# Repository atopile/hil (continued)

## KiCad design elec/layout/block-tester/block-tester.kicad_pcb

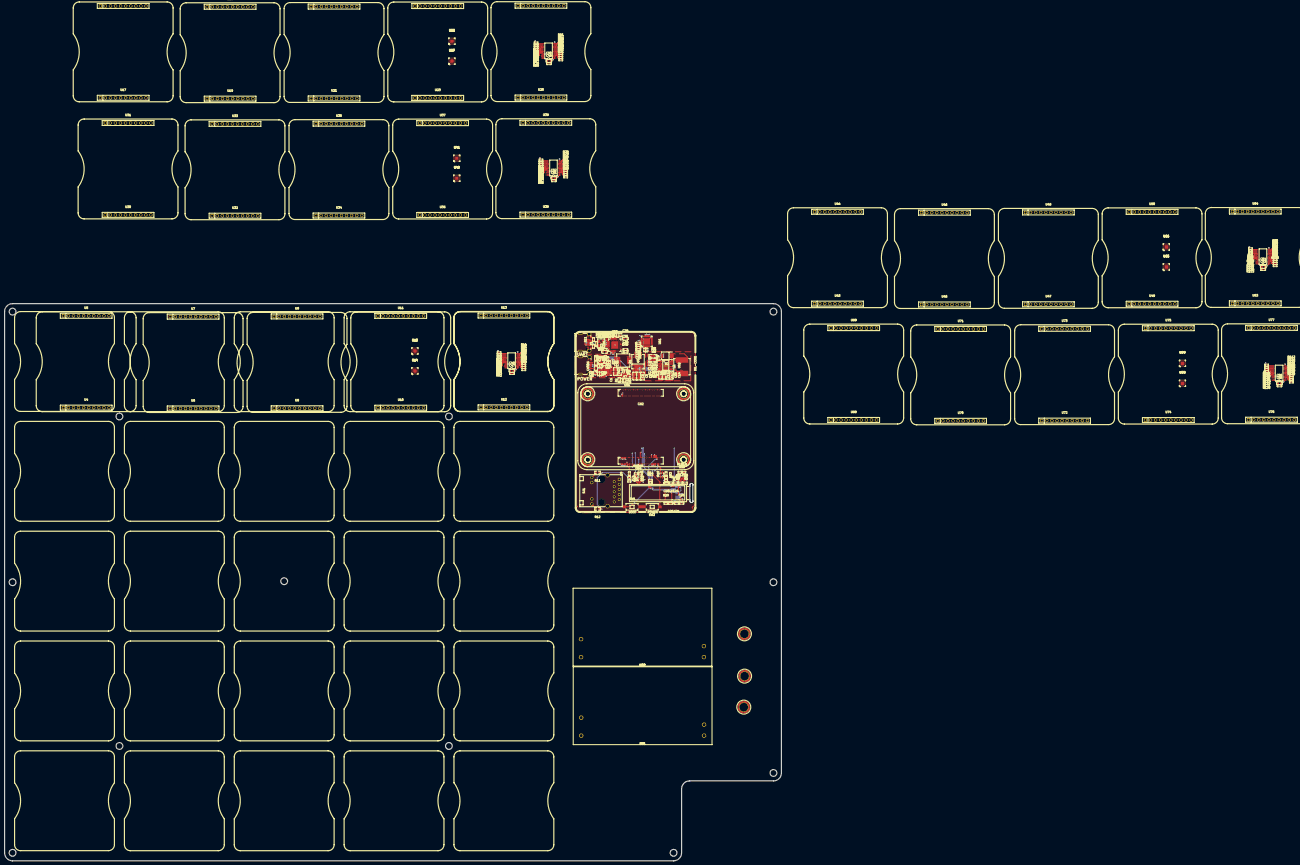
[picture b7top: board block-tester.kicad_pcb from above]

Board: 2 copper layers, 389.0 x 279.0 mm, 279 parts (0 on the bottom side), 306 nets.

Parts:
C1: 6.8nF ±10% 50V X7R; C0402-b3ef17
C2, C3, C4, C5, C6: 10µF ±10% 25V X5R; C0805-3b2e55
C7, C25, C42: 4.7µF ±20% 10V X5R; C0402-b3ef17
C8: 100nF ±10% 50V X7R; C0402-b3ef17
C9: 4.7nF ±5% 50V C0G; C0402-b3ef17
C10: 8.2pF ±5% 50V C0G; C0402-b3ef17
C11, C12, C13: 10µF ±10% 50V X5R; C0805-3b2e55
C14, C15, C16, C17: 22µF ±20% 25V X5R; C0805-3b2e55
C18, C19, C20, C21, C22, C23, C40, C44, C45: 1µF ±10% 25V X5R; C0402-b3ef17
C24, C26, C27, C28, C31, C32, C33, C34, C35, C36, C39, C41, C46, C47, C49, C51, C53, C55: 100nF ±10% 16V X7R; C0402-b3ef17
C29, C30: 10µF ±10% 10V X5R; C0603-bd72f6
C37, C38: 20pF ±5% 50V C0G; C0402-b3ef17
C43: 4.7µF ±10% 35V X5R; C0603-bd72f6
C48, C50, C52, C54, C56: 2.2µF ±10% 16V X5R; C0603-bd72f6
CN1, CN2: CONN-SMD_DF40C-100DS-0.4V-51-ceffa9
D1: SMC_L7.1-W6.2-LS8.1-RD-d9649d
D2: SMB_L4.6-W3.6-LS5.3-RD-330cb3
D3: LED0603-RD-YELLOW-5af84a
D4: LED0603-RD-c81ffb
D5: SOT-323-3_L2.1-W1.3-P1.32-LS2.1-BR-ee9edb
D6, D7: DFN1610-2_L1.6-W1.0-P1.05-RD-57a24e
L1: IND-SMD_L7.1-W6.6-48b69f
L2: IND-SMD_L8.0-W8.0_SWPA8040S-2a70f8
OLED1: OLED-SMD_N087-2832TSWYG02-H14_1-7d3a70
Q1: PDFN3333-8_L3.1-W3.2-P0.65-LS3.4-BL-33e04e
R1, R6, R13, R14, R18, R20, R26, R29, R38, R39, R40, R41, R42, R43, R44, R45, R46, R47, R48, R49, R50, R51, R52, R53, R54, R55, R56, R57, R58, R59, R60, R61, R62, R63, R64, R65, R66, R67, R68, R69, R70, R71, R72, R73, R74, R75, R76, R77, R78, R79, R80, R81, R82, R83, R84, R85, R86, R87, R88, R89, R90, R91, R92, R93, R94, R95, R96, R97, R98, R99, R100, R101, R102, R103, R104, R105, R106, R107, R108, R109, R110, R111, R112, R113, R114, R115, R116, R117, R118, R119, R120, R121, R122: 10kΩ ±1% 62.5mW; R0402-56259e
R2: 180kΩ ±1% 62.5mW; R0402-56259e
R3: 2.49kΩ ±1% 62.5mW; R0402-56259e
R4: 75kΩ ±1% 62.5mW; R0402-56259e
R5: 23.7kΩ ±1% 62.5mW; R0402-56259e
R7: 51kΩ ±1% 62.5mW; R0402-56259e
R8: 162kΩ ±1% 62.5mW; R0402-56259e
R9, R10: 2kΩ ±1% 62.5mW; R0402-56259e
R11, R12: 470Ω ±1% 100mW; R0603-ebcab9
R15: 560Ω ±1% 62.5mW; R0402-56259e
R16, R31, R34: 1kΩ ±1% 62.5mW; R0402-56259e
R17: 510kΩ ±1% 62.5mW; R0402-56259e
R19: 25.5kΩ ±1% 62.5mW; R0402-56259e
R21, R22: 5.1kΩ ±1% 62.5mW; R0402-56259e
R23, R24, R27, R28: 33kΩ ±1% 62.5mW; R0402-56259e
R25: 12kΩ ±1% 62.5mW; R0402-56259e
R30, R32, R33: 4.7kΩ ±1% 62.5mW; R0402-56259e
R35: 100kΩ ±1% 62.5mW; R0402-56259e
R36: 22kΩ ±1% 62.5mW; R0402-56259e
R37: 100Ω ±1% 62.5mW; R0402-56259e
RJ1: RJ45-TH_HR911130A-5845d4
SW1, SW2: SW-SMD_L6.0-W3.3-LS8.0-cfbaed
U1, U2, U3, U54, U55, U56, U57: SMD_BD5.6-D4.1-12eb58
U4, U5, U6, U7, U8, U9, U10, U11, U12, U13, U17, U18, U19, U20, U21, U22, U23, U24, U25, U26, U30, U31, U32, U33, U34, U35, U36, U37, U38, U39, U43, U44, U45, U46, U47, U48, U49, U50, U63, U64, U68, U69, U70, U71, U72, U73, U74, U75, U76, U77: HDR-TH_10P-P2.54-V-F-f96416
U14, U15, U27, U28, U40, U41, U65, U66, U78, U79: QFN-16_L3.0-W3.0-P0.50-BL-EP1.7-3a4c56
U16, U29, U42, U67, U80: TSSOP-24_L7.8-W4.4-P0.65-LS6.4-BL
U51: VQFN-16_L3.0-W3.0-P0.50-BL-EP1.7-62c35a
U52: SOIC-8_L5.0-W4.0-P1.27-LS6.0-BL-EP2.0-748c0f
U53: SOT-23-5_L3.0-W1.7-P0.95-LS2.8-BR-9d80aa
U58, U59: SOT-23-5_L3.0-W1.7-P0.95-LS2.8-BL
U60: SQFN-36_L6.0-W6.0-P0.50-BL-EP-5817ac
U61: WQFN-28_L5.0-W5.0-P0.50-BL-EP3.2-79d8c5
U62: QFN-24_L4.0-W4.0-P0.50-BL-EP2.8-2a85a7
U81, U82: PWRM-TH_L69.5-W39.0_LD30-23B05R2-a2c477
USB1, USB2: USB-C-SMD_TYC-324G-a50b79
X1: CRYSTAL-SMD_4P-L3.2-W2.5-BL-1-d85bc6

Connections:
A5: R21.1, USB1.A5
A6: USB2.A6, USB2.B6
BOOT: C8.1, U52.1
C1N: C20.1, OLED1.4
C1P: C20.2, OLED1.3
C2N: C21.1, OLED1.2
C2P: C21.2, OLED1.1
CC2: R22.1, USB1.B5
DISCH: R31.2, U62.9
DN1: USB2.A7, USB2.B7
Dminus: U60.1, U61.5
Dplus: U60.2, U61.4
FREQ: R4.1, U51.9
GND: C1.2, C2.2, C3.2, C4.2, C5.2, C6.2, C7.2, C9.2, C10.2, C11.2, C12.2, C13.2, C14.2, C15.2, C16.2, C17.2, C18.2, C19.2, C22.2, C23.2, C24.2, C25.2, C26.2, C27.2, C28.2, C29.2, C30.2, C31.2, C32.2, C33.2, C34.2, C35.2, C36.2, C37.2, C38.2, C39.2, C40.2, C41.2, C42.2, C43.1, C44.1, C45.1, CN1.1, CN1.4, CN1.7, CN1.11, CN1.16, CN1.21, CN1.26, CN1.30, CN1.33, CN1.37, CN1.49, CN1.65, CN1.68, CN1.71, CN1.74, CN1.79, CN1.84, CN1.89, CN1.94, CN1.97, CN1.100, CN2.4, CN2.7, CN2.10, CN2.13, CN2.16, CN2.19, CN2.22, CN2.28, CN2.31, CN2.34, CN2.37, CN2.40, CN2.43, CN2.46, CN2.49, CN2.52, CN2.55, CN2.58, CN2.61, CN2.64, CN2.67, CN2.70, CN2.73, CN2.82, CN2.85, CN2.88, CN2.91, CN2.94, CN2.97, D2.2, D5.3, D6.2, D7.2, OLED1.7, R1.2, R4.2, R6.2, R8.2, R15.2, R17.2, R18.2, R21.2, R22.2, R23.2, R24.2, R25.2, R27.2, R28.2, R29.2, RJ1.SHIELD0, RJ1.SHIELD1, SW1.2, SW2.2, U51.5, U51.6, U51.11, U51.12, U51.13, U51.17, U52.7, U52.9, U53.3, U54.1, U54.2, U54.3, U54.4, U55.1, U55.2, U55.3, U55.4, U56.1, U56.2, U56.3, U56.4, U57.1, U57.2, U57.3, U57.4, U58.2, U59.2, U60.37, U61.3, U61.29, U62.6, U62.10, U62.12, U62.13, U62.22, U62.25, USB1.1, USB1.2, USB1.3, USB1.4, USB1.A1, USB1.A12, USB1.B1, USB1.B12, USB2.1, USB2.2, USB2.3, USB2.4, USB2.A1, USB2.A12, USB2.B1, USB2.B12, X1.2, X1.4
HS_IND_CFG_SEL1: R27.1, U60.25
IREF: OLED1.12, R17.1
MDI1plus: CN1.2, RJ1.P4
MDI2plus: CN1.95, RJ1.P5
MDI3_: CN1.98, RJ1.P9
MDI3plus: CN1.99, RJ1.P8
POWER_3V3: C19.1, C24.1, C25.1, C26.1, C27.1, C28.1, C29.1, C30.1, C31.1, C32.1, C33.1, C34.1, C35.1, C36.1, OLED1.8, OLED1.13, OLED1.14, R13.2, R14.2, R16.1, R20.2, R26.2, U58.5, U60.5, U60.10, U60.15, U60.23, U60.27, U60.29, U60.36
POWER_5V: C14.1, C15.1, C16.1, C17.1, C18.1, C22.1, CN1.57, CN1.58, CN1.59, CN1.60, CN1.61, CN1.62, L2.2, R7.1, U58.1, U58.3, U59.1, U59.3
POWER_24V: C4.1, C5.1, C6.1, C11.1, C12.1, C13.1, D1.1, R2.1, U52.2
RBIAS: R25.1, U60.35
RESET_N: R26.1, U60.26
RESh: OLED1.9, R20.1
RSTh: R30.1, U61.9
RT_CLK: R8.1, U52.4
SCL_SMBCLK_CFG_SEL0: R23.1, U60.24
SDA_SMBBATA_NON_REM1: R24.1, U60.22
SS: C7.1, U51.4
SUSPENDh: R29.1, U61.11
SUSP_IND_LOCAL_PWR_NON_REM0: R28.1, U60.28
SW: C8.2, D2.1, L2.1, U52.8
USBDM_UP: U60.30, USB1.A7, USB1.B7
USBDP_UP: U60.31, USB1.A6, USB1.B6
VBUS: C43.2, C46.2, D6.1, Q1.1, Q1.2, Q1.3, R31.1, R34.1, U62.24, USB2.A4, USB2.A9, USB2.B4, USB2.B9
VBUS_EN_SNK: R36.2, U62.16
VBUS_VS_DISCH: R34.2, U62.18
Y: R10.2, U53.4
ac_in_chassis-net: U1.1, U1.2, U1.3, U1.4
ac_in_line-net: U2.1, U2.2, U2.3, U2.4
ac_in_neutral-net: U3.1, U3.2, U3.3, U3.4
column_0.base_0-gnd: U4.1, U4.4, U4.7, U4.10, U5.1, U5.4, U5.7, U5.10
column_0.base_0-hv: U5.5, U5.6
column_0.base_0-hv-1: U5.8, U5.9
column_0.base_0-hv-2: U5.2, U5.3
column_0.base_1-gnd: U6.1, U6.4, U6.7, U6.10, U7.1, U7.4, U7.7, U7.10
column_0.base_1-hv: U7.8, U7.9
column_0.base_1-hv-1: U7.5, U7.6
column_0.base_1-hv-2: U7.2, U7.3
column_0.base_2-gnd: U8.1, U8.4, U8.7, U8.10, U9.1, U9.4, U9.7, U9.10
column_0.base_2-hv: U9.8, U9.9
column_0.base_2-hv-1: U9.2, U9.3
column_0.base_2-hv-2: U9.5, U9.6
column_0.base_3-gnd: U10.1, U10.4, U10.7, U10.10, U11.1, U11.4, U11.7, U11.10
column_0.base_3-hv: U11.8, U11.9
column_0.base_3-hv-1: U11.2, U11.3
column_0.base_3-hv-2: U11.5, U11.6
column_0.base_4-gnd: U12.1, U12.4, U12.7, U12.10, U13.1, U13.4, U13.7, U13.10
column_0.base_4-hv: U13.2, U13.3
column_0.base_4-hv-1: U13.8, U13.9
column_0.base_4-hv-2: U13.5, U13.6
column_0.gpio_expander_1-VCCI: U14.1, U14.14, U14.15
column_0.gpio_expander_1-gnd: U14.6, U14.17
column_0.gpio_expander_2-RESET: U15.1, U15.14, U15.15
column_0.gpio_expander_2-gnd: U15.6, U15.17
column_0.i2c_mux-RESET_: R54.1, U16.3
column_0.i2c_mux-SC0: R38.1, U16.5
column_0.i2c_mux-SC1: R40.1, U16.7
column_0.i2c_mux-SC2: R42.1, U16.9
column_0.i2c_mux-SC3: R44.1, U16.11
column_0.i2c_mux-SC4: R46.1, U16.14
column_0.i2c_mux-SC5: R48.1, U16.16
column_0.i2c_mux-SC6: R50.1, U16.18
column_0.i2c_mux-SC7: R52.1, U16.20
column_0.i2c_mux-SD0: R39.1, U16.4
column_0.i2c_mux-SD1: R41.1, U16.6
column_0.i2c_mux-SD2: R43.1, U16.8
column_0.i2c_mux-SD3: R45.1, U16.10
column_0.i2c_mux-SD4: R47.1, U16.13
column_0.i2c_mux-SD5: R49.1, U16.15
column_0.i2c_mux-SD6: R51.1, U16.17
column_0.i2c_mux-SD7: R53.1, U16.19
column_1.base_0-gnd: U17.1, U17.4, U17.7, U17.10, U18.1, U18.4, U18.7, U18.10
column_1.base_0-hv: U18.2, U18.3
column_1.base_0-hv-1: U18.5, U18.6
column_1.base_0-hv-2: U18.8, U18.9
column_1.base_1-gnd: U19.1, U19.4, U19.7, U19.10, U20.1, U20.4, U20.7, U20.10
column_1.base_1-hv: U20.2, U20.3
column_1.base_1-hv-1: U20.5, U20.6
column_1.base_1-hv-2: U20.8, U20.9
column_1.base_2-gnd: U21.1, U21.4, U21.7, U21.10, U22.1, U22.4, U22.7, U22.10
column_1.base_2-hv: U22.2, U22.3
column_1.base_2-hv-1: U22.8, U22.9
column_1.base_2-hv-2: U22.5, U22.6
column_1.base_3-gnd: U23.1, U23.4, U23.7, U23.10, U24.1, U24.4, U24.7, U24.10
column_1.base_3-hv: U24.2, U24.3
column_1.base_3-hv-1: U24.8, U24.9
column_1.base_3-hv-2: U24.5, U24.6
column_1.base_4-gnd: U25.1, U25.4, U25.7, U25.10, U26.1, U26.4, U26.7, U26.10
column_1.base_4-hv: U26.8, U26.9
column_1.base_4-hv-1: U26.5, U26.6
column_1.base_4-hv-2: U26.2, U26.3
column_1.gpio_expander_1-RESET: U27.1, U27.14, U27.15
column_1.gpio_expander_1-gnd: U27.6, U27.17
column_1.gpio_expander_2-VCCP: U28.1, U28.14, U28.15
column_1.gpio_expander_2-gnd: U28.6, U28.17
column_1.i2c_mux-RESET_: R71.1, U29.3
column_1.i2c_mux-SC0: R55.1, U29.5
column_1.i2c_mux-SC1: R57.1, U29.7
column_1.i2c_mux-SC2: R59.1, U29.9
column_1.i2c_mux-SC3: R61.1, U29.11
column_1.i2c_mux-SC4: R63.1, U29.14
column_1.i2c_mux-SC5: R65.1, U29.16
column_1.i2c_mux-SC6: R67.1, U29.18
column_1.i2c_mux-SC7: R69.1, U29.20
column_1.i2c_mux-SD0: R56.1, U29.4
column_1.i2c_mux-SD1: R58.1, U29.6
column_1.i2c_mux-SD2: R60.1, U29.8
column_1.i2c_mux-SD3: R62.1, U29.10
column_1.i2c_mux-SD4: R64.1, U29.13
column_1.i2c_mux-SD5: R66.1, U29.15
column_1.i2c_mux-SD6: R68.1, U29.17
column_1.i2c_mux-SD7: R70.1, U29.19
column_2.base_0-gnd: U30.1, U30.4, U30.7, U30.10, U31.1, U31.4, U31.7, U31.10
column_2.base_0-hv: U31.2, U31.3
column_2.base_0-hv-1: U31.5, U31.6
column_2.base_0-hv-2: U31.8, U31.9
column_2.base_1-gnd: U32.1, U32.4, U32.7, U32.10, U33.1, U33.4, U33.7, U33.10
column_2.base_1-hv: U33.2, U33.3
column_2.base_1-hv-1: U33.5, U33.6
column_2.base_1-hv-2: U33.8, U33.9
column_2.base_2-gnd: U34.1, U34.4, U34.7, U34.10, U35.1, U35.4, U35.7, U35.10
column_2.base_2-hv: U35.5, U35.6
column_2.base_2-hv-1: U35.2, U35.3
column_2.base_2-hv-2: U35.8, U35.9
column_2.base_3-gnd: U36.1, U36.4, U36.7, U36.10, U37.1, U37.4, U37.7, U37.10
column_2.base_3-hv: U37.8, U37.9
column_2.base_3-hv-1: U37.5, U37.6
column_2.base_3-hv-2: U37.2, U37.3
column_2.base_4-gnd: U38.1, U38.4, U38.7, U38.10, U39.1, U39.4, U39.7, U39.10
column_2.base_4-hv: U39.5, U39.6
column_2.base_4-hv-1: U39.8, U39.9
column_2.base_4-hv-2: U39.2, U39.3
column_2.gpio_expander_1-VCCI: U40.1, U40.14, U40.15
column_2.gpio_expander_1-gnd: U40.6, U40.17
column_2.gpio_expander_2-VCCP: U41.1, U41.14, U41.15
column_2.gpio_expander_2-gnd: U41.6, U41.17
column_2.i2c_mux-RESET_: R88.1, U42.3
column_2.i2c_mux-SC0: R72.1, U42.5
column_2.i2c_mux-SC1: R74.1, U42.7
column_2.i2c_mux-SC2: R76.1, U42.9
column_2.i2c_mux-SC3: R78.1, U42.11
column_2.i2c_mux-SC4: R80.1, U42.14
column_2.i2c_mux-SC5: R82.1, U42.16
column_2.i2c_mux-SC6: R84.1, U42.18
column_2.i2c_mux-SC7: R86.1, U42.20
column_2.i2c_mux-SD0: R73.1, U42.4
column_2.i2c_mux-SD1: R75.1, U42.6
column_2.i2c_mux-SD2: R77.1, U42.8
column_2.i2c_mux-SD3: R79.1, U42.10
column_2.i2c_mux-SD4: R81.1, U42.13
column_2.i2c_mux-SD5: R83.1, U42.15
column_2.i2c_mux-SD6: R85.1, U42.17
column_2.i2c_mux-SD7: R87.1, U42.19
column_3.base_0-gnd: U43.1, U43.4, U43.7, U43.10, U44.1, U44.4, U44.7, U44.10
column_3.base_0-hv: U44.2, U44.3
column_3.base_0-hv-1: U44.5, U44.6
column_3.base_0-hv-2: U44.8, U44.9
column_3.base_1-gnd: U45.1, U45.4, U45.7, U45.10, U46.1, U46.4, U46.7, U46.10
column_3.base_1-hv: U46.8, U46.9
column_3.base_1-hv-1: U46.2, U46.3
column_3.base_1-hv-2: U46.5, U46.6
column_3.base_2-gnd: U47.1, U47.4, U47.7, U47.10, U48.1, U48.4, U48.7, U48.10
column_3.base_2-hv: U48.2, U48.3
column_3.base_2-hv-1: U48.8, U48.9
column_3.base_2-hv-2: U48.5, U48.6
column_3.base_3-gnd: U49.1, U49.4, U49.7, U49.10, U50.1, U50.4, U50.7, U50.10
column_3.base_3-hv: U50.5, U50.6
column_3.base_3-hv-1: U50.8, U50.9
column_3.base_3-hv-2: U50.2, U50.3
column_3.base_4-gnd: U63.1, U63.4, U63.7, U63.10, U64.1, U64.4, U64.7, U64.10
column_3.base_4-hv: U64.8, U64.9
column_3.base_4-hv-1: U64.2, U64.3
column_3.base_4-hv-2: U64.5, U64.6
column_3.gpio_expander_1-VCCI: U65.1, U65.14, U65.15
column_3.gpio_expander_1-gnd: U65.6, U65.17
column_3.gpio_expander_2-VCCP: U66.1, U66.14, U66.15
column_3.gpio_expander_2-gnd: U66.6, U66.17
column_3.i2c_mux-RESET_: R105.1, U67.3
column_3.i2c_mux-SC0: R89.1, U67.5
column_3.i2c_mux-SC1: R91.1, U67.7
column_3.i2c_mux-SC2: R93.1, U67.9
column_3.i2c_mux-SC3: R95.1, U67.11
column_3.i2c_mux-SC4: R97.1, U67.14
column_3.i2c_mux-SC5: R99.1, U67.16
column_3.i2c_mux-SC6: R101.1, U67.18
column_3.i2c_mux-SC7: R103.1, U67.20
column_3.i2c_mux-SD0: R90.1, U67.4
column_3.i2c_mux-SD1: R92.1, U67.6
column_3.i2c_mux-SD2: R94.1, U67.8
column_3.i2c_mux-SD3: R96.1, U67.10
column_3.i2c_mux-SD4: R98.1, U67.13
column_3.i2c_mux-SD5: R100.1, U67.15
column_3.i2c_mux-SD6: R102.1, U67.17
column_3.i2c_mux-SD7: R104.1, U67.19
column_4.base_0-gnd: U68.1, U68.4, U68.7, U68.10, U69.1, U69.4, U69.7, U69.10
column_4.base_0-hv: U69.5, U69.6
column_4.base_0-hv-1: U69.2, U69.3
column_4.base_0-hv-2: U69.8, U69.9
column_4.base_1-gnd: U70.1, U70.4, U70.7, U70.10, U71.1, U71.4, U71.7, U71.10
column_4.base_1-hv: U71.8, U71.9
column_4.base_1-hv-1: U71.2, U71.3
column_4.base_1-hv-2: U71.5, U71.6
column_4.base_2-gnd: U72.1, U72.4, U72.7, U72.10, U73.1, U73.4, U73.7, U73.10
column_4.base_2-hv: U73.2, U73.3
column_4.base_2-hv-1: U73.8, U73.9
column_4.base_2-hv-2: U73.5, U73.6
column_4.base_3-gnd: U74.1, U74.4, U74.7, U74.10, U75.1, U75.4, U75.7, U75.10
column_4.base_3-hv: U75.8, U75.9
column_4.base_3-hv-1: U75.5, U75.6
column_4.base_3-hv-2: U75.2, U75.3
column_4.base_4-gnd: U76.1, U76.4, U76.7, U76.10, U77.1, U77.4, U77.7, U77.10
column_4.base_4-hv: U77.5, U77.6
column_4.base_4-hv-1: U77.2, U77.3
column_4.base_4-hv-2: U77.8, U77.9
column_4.gpio_expander_1-RESET: U78.1, U78.14, U78.15
column_4.gpio_expander_1-gnd: U78.6, U78.17
column_4.gpio_expander_2-RESET: U79.1, U79.14, U79.15
column_4.gpio_expander_2-gnd: U79.6, U79.17
column_4.i2c_mux-RESET_: R122.1, U80.3
column_4.i2c_mux-SC0: R106.1, U80.5
column_4.i2c_mux-SC1: R108.1, U80.7
column_4.i2c_mux-SC2: R110.1, U80.9
column_4.i2c_mux-SC3: R112.1, U80.11
column_4.i2c_mux-SC4: R114.1, U80.14
column_4.i2c_mux-SC5: R116.1, U80.16
column_4.i2c_mux-SC6: R118.1, U80.18
column_4.i2c_mux-SC7: R120.1, U80.20
column_4.i2c_mux-SD0: R107.1, U80.4
column_4.i2c_mux-SD1: R109.1, U80.6
column_4.i2c_mux-SD2: R111.1, U80.8
column_4.i2c_mux-SD3: R113.1, U80.10
column_4.i2c_mux-SD4: R115.1, U80.13
column_4.i2c_mux-SD5: R117.1, U80.15
column_4.i2c_mux-SD6: R119.1, U80.17
column_4.i2c_mux-SD7: R121.1, U80.19
gate: Q1.4, R35.1, R36.1, R37.1
gnd: C51.2, C52.2, U42.1, U42.2, U42.12, U42.21
gnd-1: C49.2, C50.2, U29.1, U29.2, U29.12, U29.21
gnd-2: C53.2, C54.2, U67.1, U67.2, U67.12, U67.21
gnd-3: C47.2, C48.2, U16.1, U16.2, U16.12, U16.21
gnd-4: C55.2, C56.2, U80.1, U80.2, U80.12, U80.21
hil_core-hv: CN1.39, CN1.42, CN1.43, D3.2, D4.2, R11.1, R12.1, U53.5
hil_core-line: CN1.86, U61.24
hil_core-line-1: CN1.23, OLED1.11, R14.1
hil_core-line-2: CN1.73, U61.25
hil_core-line-3: CN1.77, OLED1.10, R13.1
hil_core-line-4: CN1.75, U61.26
hil_core-line-5: CN1.25, U61.23
hil_core.boost_24v-COMP: R3.1, U51.7
hil_core.boost_24v-FB: R1.1, R2.2, U51.8
hil_core.boost_24v-net: C1.1, R3.2
hil_core.buck_5v-COMP: C10.1, R5.1, U52.6
hil_core.buck_5v-FB: R6.1, R7.2, U52.5
hil_core.buck_5v-net: C9.1, R5.2
hil_core.controller-pins[5]: CN1.3, RJ1.P7
hil_core.controller-pins[8]: CN1.96, RJ1.P6
hil_core.controller-pins[9]: CN1.5, RJ1.P3
hil_core.controller-pins[11]: CN1.6, RJ1.P2
hil_core.controller-pins[14]: CN1.93, RJ1.12
hil_core.controller-pins[16]: CN1.92, RJ1.13
hil_core.controller-pins[92]: CN1.54, SW1.1
hil_core.controller.cm5-cathode: D3.1, R9.1
hil_core.controller.cm5-cathode-1: D4.1, R10.1
hil_core.controller.cm5-pins[20]: CN1.90, R9.2
hil_core.controller.cm5-pins[89]-1: CN1.44, CN1.45
hil_core.controller.cm5-pins[94]: CN1.53, U53.2
hil_core.controller.rj45-anode: R11.2, RJ1.11
hil_core.controller.rj45-anode-1: R12.2, RJ1.14
hil_core.ldo_3v3-ADJ_NC: R15.1, R16.2, U58.4
hil_core.oled.regulator_4v-ADJ_NC: R18.1, R19.2, U59.4
hil_core.usbpd-hv: R32.2, R33.2
hil_core.usbpd-line: R33.1, U62.8
hil_core.usbpd-line-1: D5.1, U62.1, U62.2, USB2.A5
hil_core.usbpd-line-2: R32.1, U62.7
hil_core.usbpd-line-3: D5.2, U62.4, U62.5, USB2.B5
hil_core.usbpd.pd_controller-hv: C44.2, U62.21
hil_core.usbpd.pd_controller-hv-1: C45.2, U62.23
hil_core.usbpd.pd_controller-net: C46.1, R37.2
hv: C55.1, C56.1, R106.2, R107.2, R108.2, R109.2, R110.2, R111.2, R112.2, R113.2, R114.2, R115.2, R116.2, R117.2, R118.2, R119.2, R120.2, R121.2, R122.2, U80.24
hv-1: C41.1, C42.1, R30.2, U61.6
hv-2: C39.1, C40.1, U61.7, U61.8, USB1.A4, USB1.A9, USB1.B4, USB1.B9
hv-3: C53.1, C54.1, R89.2, R90.2, R91.2, R92.2, R93.2, R94.2, R95.2, R96.2, R97.2, R98.2, R99.2, R100.2, R101.2, R102.2, R103.2, R104.2, R105.2, U67.24
hv-4: C47.1, C48.1, R38.2, R39.2, R40.2, R41.2, R42.2, R43.2, R44.2, R45.2, R46.2, R47.2, R48.2, R49.2, R50.2, R51.2, R52.2, R53.2, R54.2, U16.24
hv-5: C2.1, C3.1, D7.1, L1.1, Q1.5, Q1.6, Q1.7, Q1.8, Q1.9, R35.2, U51.2, U51.3
hv-6: C23.1, OLED1.5, R19.1, U59.5
hv-7: C51.1, C52.1, R72.2, R73.2, R74.2, R75.2, R76.2, R77.2, R78.2, R79.2, R80.2, R81.2, R82.2, R83.2, R84.2, R85.2, R86.2, R87.2, R88.2, U42.24
hv-8: C49.1, C50.1, R55.2, R56.2, R57.2, R58.2, R59.2, R60.2, R61.2, R62.2, R63.2, R64.2, R65.2, R66.2, R67.2, R68.2, R69.2, R70.2, R71.2, U29.24
pins[2]: CN2.99, U60.3
pins[4]: CN2.98, U60.4
pins[91]: CN1.46, SW2.1
switching_node: D1.2, L1.2, U51.1, U51.15, U51.16
xin: C37.1, U60.33, X1.1
xout: C38.1, U60.32, X1.3

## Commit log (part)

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2025-02-17 "Fix test_output_voltage_per_cell"
2025-02-17 "i2c driver updates, test output function adjusted"
2025-02-17 Ensure chart_path dir
2025-02-17 from git repo root
2025-02-17 `run_on` -> `runs_on`
2025-02-17 Update ato build workflow triggers
2025-02-17 `runs_on` marker and pytest in CI (#32)
    * Add `runs_on` marker, which skips tests unable to run on the current machine
    * Mark test_cell's tests as only working on `chunky-otter`
    * Add pytest CI job
    * Ensure chart_path dir
    * `run_on` -> `runs_on`
    * Update ato build workflow triggers
2025-02-17 Create ABC for AsyncSMBus instead of type alias
2025-02-17 somewhat working, before i change a bunch
2025-02-18 Make base class fully abstract and add tiny doc to runtest
2025-02-18 Fix default hil_configs_dir
2025-02-18 Use hostname instead of socket, since we'll provision the systems with their pet_names instead
2025-02-18 Improve performance of get_name
2025-02-18 Config persistence (#33)
    * Create ABC for AsyncSMBus instead of type alias
    * Create and use common configs
    * Make base class fully abstract and add tiny doc to runtest
    * Fix default hil_configs_dir
    * Use hostname instead of socket, since we'll provision the systems with their pet_names instead
    * Improve the distribution of pet names
2025-02-18 Fix test_output_voltage_per_cell too
2025-02-18 Loosen test_buck_voltage
2025-02-18 Update test_exception_table
2025-02-18 comment out net name overrides, build 8ch cell
2025-02-18 Calibration and config upgrades
2025-02-18 Remove dud config
2025-02-18 Further improve config robustness
2025-02-18 collect runs_on
2025-02-18 HeterogenousLoadScheduling wip
2025-02-18 collect tests on controller to determine affinity
2025-02-18 group nodeids
2025-02-18 fix distribution to local
2025-02-18 configure node
2025-02-18 collect tests on workers
2025-02-18 fix double collection
2025-02-18 rename
2025-02-18 check_schedule
2025-02-18 route i2c
2025-02-19 partially completed moving calibrate to a class
2025-02-19 unable to resolve bus params
2025-02-19 iter_markers
2025-02-19 calibration working, powersupply + 32 data points
2025-02-19 Restore buck voltage calculation and add docstring to calibration test
    - Uncomment and re-enable buck voltage calculation in cell driver
    - Add descriptive docstring to calibration test function
2025-02-19 WIP: proof of concept
2025-02-19 Test for tomorrow
2025-02-20 "resloved comments"
2025-02-20 final comments resolved
2025-02-20 "resolved comments to do with framework.py"
2025-02-20 reinstituted test_cell_calibration to run by default
2025-02-20 final resolutions
2025-02-20 Test calibrate (#37)
    * partially completed moving calibrate to a class
    * calibration working, powersupply + 32 data points
    * Restore buck voltage calculation and add docstring to calibration test
    - Uncomment and re-enable buck voltage calculation in cell driver
    - Add descriptive docstring to calibration test function
    * made adjustments according to comments
2025-02-25 remote test exec
2025-02-25 process all tests
2025-02-25 fix runtime env
2025-02-25 structured events
2025-02-25 better item lookup
2025-02-25 Add basic server deps
2025-02-25 Add cspell
2025-02-25 Add cloudpickle and multipart files
2025-02-25 ray -> http (wip)
2025-02-25 init api client
2025-02-25 fastapi[standard]
2025-02-25 binary data handling
2025-02-25 attrs -> dataclasses
2025-02-26 init client
2025-02-26 Add empty tests for testing testing
2025-02-26 WIP: mostly working worker
2025-02-26 WIP: dist plugin disting
2025-02-26 WIP; dist worker appears to be working
2025-02-26 No node_ids in URL
2025-02-26 Fix session_id for worker API
2025-02-26 fix api usage
2025-02-26 fix adding new test report
2025-02-26 Overly log
2025-02-26 Ensure we run both tests
2025-02-26 per-phase test reports
2025-02-26 TestPhase enum
2025-02-26 more enums
2025-02-26 rm duplicate model
2025-02-26 artifacts (wip)
2025-02-26 artifacts
2025-02-26 Add supabase dependency
2025-02-26 Add comments on speedup of zipping
2025-02-26 Add message for largest files
2025-02-26 Synchronous worker API
2025-02-26 Use worker_id field, rather than column ID, and add heartbeat
2025-02-26 init supervisor
2025-02-27 supervised test execution
2025-02-27 connect core gnd to input power gnd
2025-02-27 api url from env
2025-02-27 Move worker seen into sequence of worker//session instead of specific registration
2025-03-10 update syntax, delete vendored packages
2025-03-10 build and re-link layouts
2025-03-12 fix error in config
2025-03-12 HIL Building
2025-03-12 fix layout issue
2025-03-12 Fix address bit issue, update layouts
2025-03-12 update i2c relay
2025-03-14 Update layouts
2025-03-14 building frozen
2025-03-14 reduce led brightness on buck-boost indicator leds
2025-03-14 add pin 1 marker to usbpd module
2025-03-17 swap to relay with 20k in stock, through hole not smt
2025-03-17 WIP - split up modules
2025-03-17 update relay layout
2025-03-17 remove space-bms-hil from ato.yaml
2025-03-17 USB UART block
2025-03-17 rename everything cm5
2025-03-17 cleanup CM4/5 layout dir and add mounting holes
2025-03-17 map i2c connections
2025-03-17 add extra i2c interfaces to ato definiton
2025-03-17 fix link light led polarity
2025-03-18 update layout, rename layout files with CM5 prefix
2025-03-18 design usb hub
2025-03-18 power switch
2025-03-18 Init docs
2025-03-18 Init docs (#55)
2025-03-18 Fix static build
2025-03-18 Fix docs build (#56)
    * Fix static build
    * Add a link to keep link checker happy
2025-03-18 Fix gnd issue
2025-03-18 upgrade to kicad 9
2025-03-18 Add debug info
2025-03-18 Add debug info (#57)
2025-03-18 main -> refs/heads/main (#58)
2025-03-18 Simpler docs build without mike
2025-03-18 Simpler docs build without mike (#59)
2025-03-18 Remove mike from mkdocs.yml config (#60)
2025-03-18 Mimic starter workflow from github
2025-03-18 Mimic starter workflow from github (#61)
2025-03-19 update core layout
2025-03-19 Save working config.txt
2025-03-19 Add bring up info for RPi device tree config
2025-03-19 Fix spelling complaints
2025-03-19 Move space-bms-hil design to examples/
2025-03-19 add connectors
2025-03-19 Remove space-bms-build
2025-03-19 fix build warnings
2025-03-19 update layouts to kicad 9
2025-03-19 update LED gpio pin
2025-03-19 restore layout files
2025-03-19 move cellsim to examples directory and remove elec/src/examples
2025-03-19 Cleanup layout
2025-03-19 Configure CAN
2025-03-20 Add SpaceBMSV1Hil, mcp4728 driver and first tests for it
2025-03-20 Add base mcp4728 implementation from adafruit
2025-03-20 finished layout + updated CI image tag
2025-03-20 fix build name for uart bridge in ato.yaml
2025-03-20 fix shorts in HIL core
2025-03-20 update HIL core layout, again
2025-03-20 update usb-uart to kicad 9
2025-03-20 Update ato-build.yml
    - use main (kicad 9 support now merging)
    - remove envars for lazy mif hack
2025-03-20 Fix githash capitalization
2025-03-20 update n-fet part for stock
2025-03-21 Update cell layouts
2025-03-21 Add page on test tools
2025-03-21 Grammer and spelling
2025-03-21 Name tool categories
2025-03-21 Add docs on index and tools philosophy (#66)
    * Add page on test tools
    * Grammer and spelling
    * Name tool categories
    * Add features to index page
2025-03-21 Add spelling for more jargon
2025-03-21 Update Docs
2025-03-21 Update Docs (#68)
2025-03-21 cosmetic fixes
2025-03-21 create components
2025-03-22 layout complete
2025-03-22 add logo
2025-03-22 remove cell changes
2025-03-22 heater controller layout
2025-03-22 remove heater controller build
2025-03-24 Add isolation cut in CAN coms, route traces for proper clearance
2025-03-24 add isolation rating marking
2025-03-24 undo changes to studs
2025-03-24 add labels
2025-03-24 Update atopile to 3.20 (#73)
2025-03-24 Tidy relay
2025-03-24 Improve CAN termination
2025-03-24 GPIO 6 isn't an SPI interrupt, it's just a GPIO that happens to be useful as an interrupt for the CAN controller
2025-03-25 Add gridfinity 3x100mm boardshape
2025-03-25 add pretty outline
2025-03-25 Attach nets to zones on template board
2025-03-25 route 20W supply
2025-03-26 Layout updated
2025-03-26 Add CANJAY
2025-03-26 Tidy relay (#75)
2025-03-26 routing
2025-03-28 fix mounting holes for cm5
2025-03-28 fix led isolation and DRC errors
2025-03-28 fix DRCs in hil core
2025-03-28 attach reference input to ADC
2025-03-28 increase uVault heater power ~30%
2025-03-28 remove vendored tca9548a, make thermistor 8ch block, make saleae debug header layout
2025-03-29 tidy up silkscreen
2025-03-29 more tidying
2025-03-29 fix config format
2025-03-30 Fix board shapes and CAN termination
2025-03-30 drc fixes
2025-03-31 Fix gnd routing for cellsim block
2025-03-31 initial placement
2025-04-01 Checkin for layout
2025-04-01 update buck-boost
2025-04-01 kicad parse error
2025-04-01 connect CAN, remove unused builds
2025-04-02 Update tools.md (#84)
2025-04-02 pin 33 should be connected to power_in, not power_out
2025-04-03 Debug fw
2025-04-03 Addressing PR comments
2025-04-04 building locally to fix frozen builds
2025-04-04 Simplify the opener enough to keep it
2025-04-04 Split into explicit `.open()` and `.handle()` functions to clarify behavior
2025-04-04 Move test_mcp4728 to test_drivers
2025-04-04 Correct DIR pins
2025-04-04 devboard for black magic probe
2025-04-04 Build everything with ordered params to fix frozen builds
2025-04-07 docs -> mintlify (#88)
2025-04-08 demo
2025-04-09 fw bringup checkin, still kinda seems broken
2025-04-09 from testing, it doesnt work very well without traces
2025-04-09 Add release github action and package metadata
2025-04-10 WIP: upgrade all the imports to use new ato packages
2025-04-11 Add CLI for petnames
2025-04-11 Add CLI for petnames (#92)
2025-04-11 Scrub remaining dependency upgrades
2025-04-11 Use run-atopile for CI
2025-04-11 Upgrade to use setup-atopile
2025-04-11 ato sync before building
2025-04-11 Fix release version
2025-04-11 Add release github action and package metadata (#90)
    * Add release github action and package metadata
    * WIP: upgrade all the imports to use new ato packages
    * Bump atopile version to 0.4.0
    * Scrub remaining dependency upgrades
    * Use run-atopile for CI
    * Upgrade to use setup-atopile
2025-04-11 Release with main atopile (#93)
2025-04-11 Use main atopile-version as well
2025-04-11 Use main atopile for publishing (#94)
    * Release with main atopile
    * Use main atopile-version as well
2025-04-11 Add release permissions (#95)
2025-04-16 CANJay SW bringup
2025-04-16 Increased wait time after enabling reverse mode (#91)
2025-04-16 CANJay SW bringup (#96)
2025-04-16 add pin headers dep, make build targets and psu fixtures
2025-04-18 Update README.md (#98)
2025-04-18 add driver for tca6408 and refactor cell to use it
2025-04-18 passing tests on cellsimv2
2025-04-18 Cleanup layout for usb hub and usb-uart, add CM5 controller heatsink outline
2025-04-19 checkin on thermistor emulation
2025-04-21 Update CANJay layout
2025-04-21 swap to DB9 connector
2025-04-21 Cellsim-16ch layout checkin
2025-04-22 Cellsim-16Ch layout complete
2025-04-22 Disable space-bms-hil build
2025-04-22 update address pin on analog out, update led value on relay
2025-04-22 layout update for can coms block
2025-04-22 Update layout for analog in block
2025-04-22 update layout for OLED
2025-04-22 Update saleae header resistance
2025-04-22 Remove old params
2025-04-22 build frozen
2025-04-23 upgrade dependencies
2025-04-23 reverting remove gnd from i2c
2025-04-23 Cleanup comments
2025-04-24 Run ato-build whenever any ato files change
2025-04-24 Run ato-build whenever any ato files change (#103)
2025-04-24 Correct the DB9 CAN pinout to use GND on pin 3
2025-04-24 Correct the DB9 CAN pinout to use GND on pin 3 (#104)
    * Correct the DB9 CAN pinout to use GND on pin 3
    * Update layout for GND pins in DB9 connector
2025-04-24 update layout with pinout change for can connector
2025-04-30 add addressor to ads1219 adc
2025-05-01 updates for i2c addressing
2025-05-01 update cell with addressing
2025-05-08 cleanup
2025-05-08 Update power connections on HV i2c isolator
2025-05-08 Fix ATX power supply pinout
2025-05-19 Fix addressor issues and layout relinking
2025-05-19 fix 8ch layout
